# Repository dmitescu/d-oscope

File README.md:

# d-oscope
Digital oscilloscope project, which can be done with medium knowledge in MCUs and programming.

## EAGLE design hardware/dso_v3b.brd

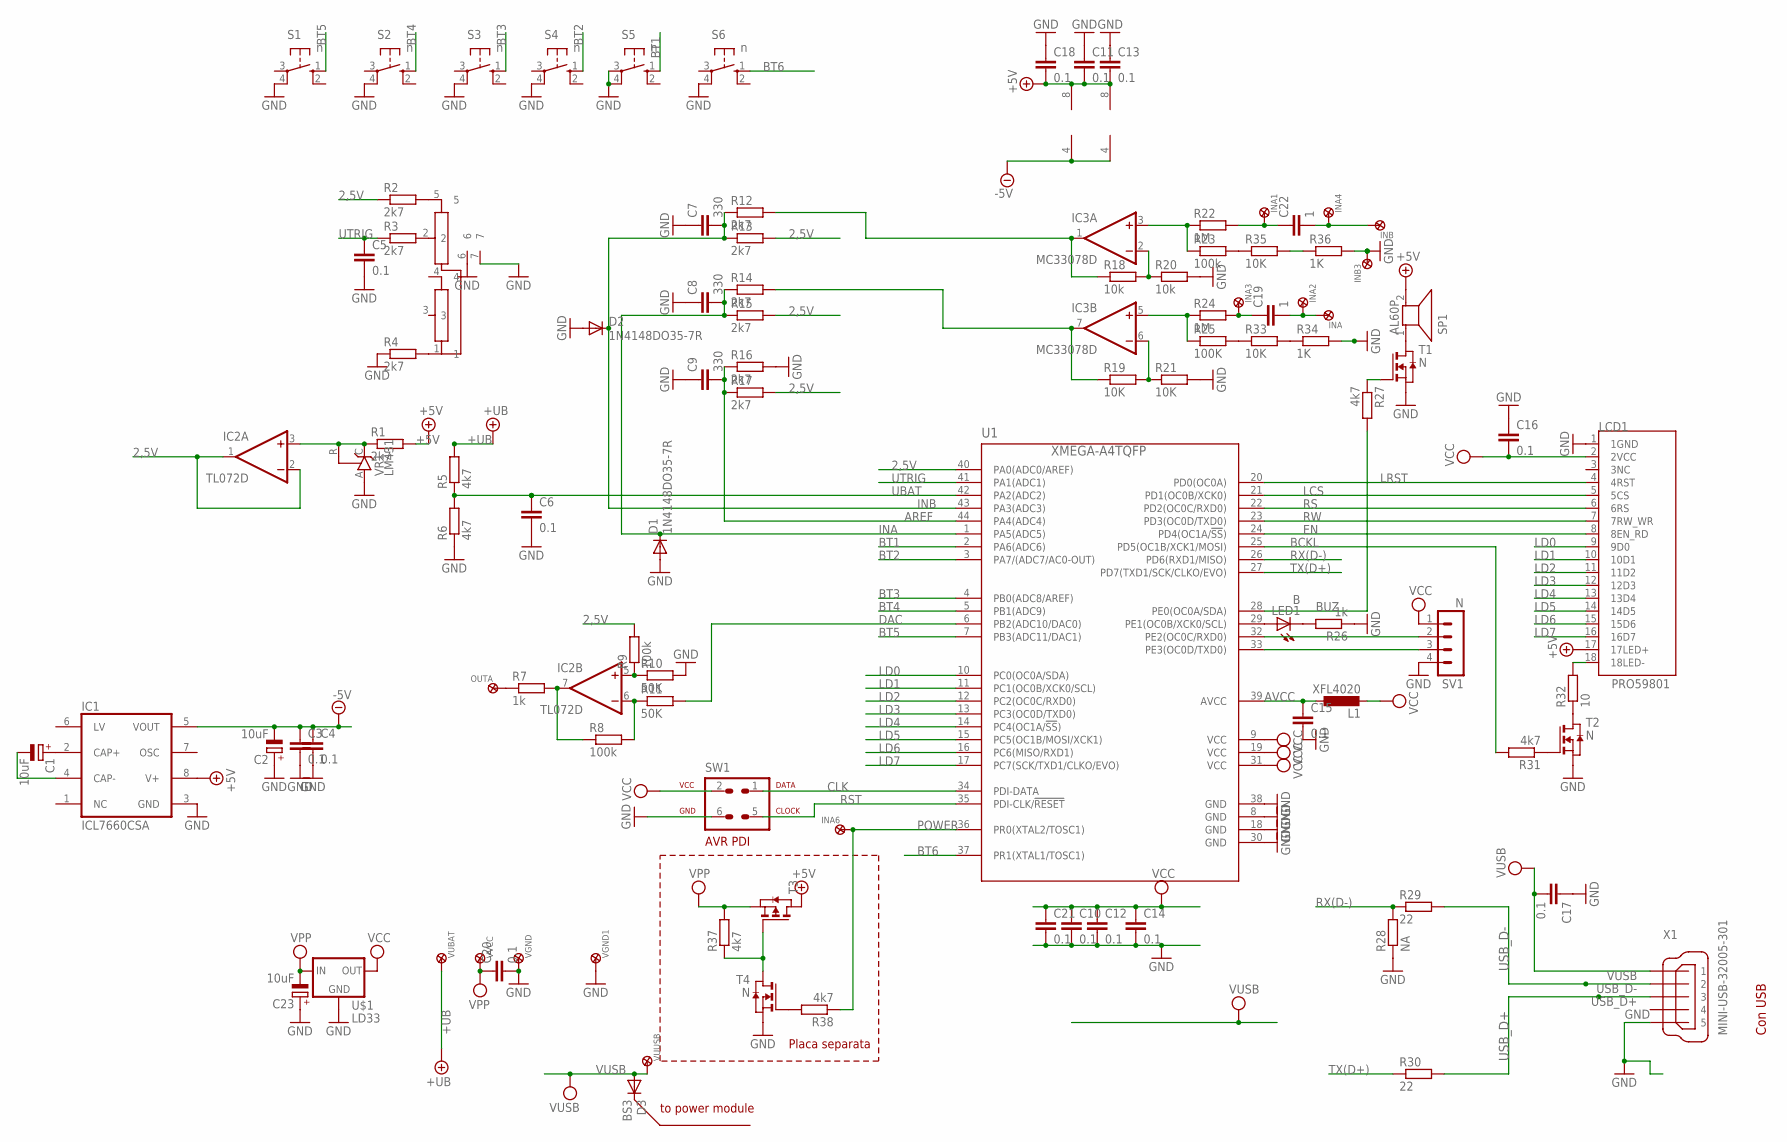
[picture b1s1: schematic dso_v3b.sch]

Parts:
C1, C2, C23: 10uF; CT3528
C3, C4, C5, C6, C10, C11, C12, C14, C15, C16, C18: 0.1; C0603
C7, C8, C9: 330; C025-024X044
C13: 0.1; SMD_SPECIAL
C17: 0.1; C1206
C19, C22: 1; C0603
C20, C21: 0.1; C0805
D1, D2: 1N4148DO35-7R; DO35-7R
D3: BS3; DO35-7R
IC1: ICL7660CSA; SO08
IC2: TL072D; SO08
IC3: MC33078D; SO08
INA, INA6: PADR1; LP1
INA1, INA2, INA3, INA4: PADR; LP
INB, INB3: PADR1; LP1
L1: XFL4020
LCD1: PRO59801; PRO59801L
LED1: B; LED3MM
OUTA: PADR1; LP1
P1: POT5P
R1: 2k7; 0204/7
R2, R3, R13, R15: 2k7; R0603
R4, R12, R14, R16, R17: 2k7; SMD_SPECIAL
R5, R6, R31, R37, R38: 4k7; R0603
R7, R26: 1k; R0603
R8, R9, R23: 100k; R0805
R10: 50K; R0805
R11: 50K; SMD_SPECIAL
R18, R20: 10k; R0805
R19, R21, R33, R35: 10K; R0805
R22, R24: 1M; R0805
R25: 100K; R0603
R27: 4k7; 0204/7
R28: NA; R0603
R29, R30: 22; R0603
R32: 10; SMD_SPECIAL
R34, R36: 1K; R0603
S1, S2, S3, S4, S5, S6: n; B3F-10XX
SP1: AL60P
SV1: N; MA04-1R
SW1: AVR-PDIS; AVR-ISP-6S
T1, T2, T4: N; SOT-23
T3: PMOSSOT23; SOT-23
U1: XMEGA-A4TQFP; TQFP44
U$1: LD33; SOT223
VGND, VGND1: PADR1; LP1
VR1: LM431; TO92-CLP
VUBAT: PADR1; LP1
VUUSB: PADR1; LP1
VVCC: PADR1; LP1
X1: MINI-USB-32005-301; 32005-301

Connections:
2,5V: IC2.1 (OUT), IC2.2 (-IN), R2.1, R9.2, R13.2, R15.2, R17.4 (2), U1.40 (PA0(ADC0/AREF))
+5V: C11.2, C13.4 (2), C18.2, IC1.8 (V+), IC2.8 (V+), IC3.8 (V+), LCD1.17 (17LED+), R1.2, SP1.2, T3.1 (D)
+UB: R5.2, VUBAT.P$1
-5V: C2.-, C3.1, C4.1, IC1.5 (VOUT), IC2.4 (V-), IC3.4 (V-)
AREF: C9.2, R16.3 (1), R17.3 (1), U1.44 (PA4(ADC4))
AVCC: C15.1, L1.P$1 (1), U1.39 (AVCC)
BCKL: R31.2, U1.25 (PD5(OC1B/XCK1/MOSI))
BT1: S5.1 (S), U1.2 (PA6(ADC6))
BT2: S4.1 (S), U1.3 (PA7/(ADC7/AC0-OUT))
BT3: S3.1 (S), U1.4 (PB0(ADC8/AREF))
BT4: S2.1 (S), U1.5 (PB1(ADC9))
BT5: S1.1 (S), U1.7 (PB3(ADC11/DAC1))
BT6: S6.1 (S), U1.37 (PR1(XTAL1/TOSC1))
BUZ: R27.2, U1.28 (PE0(OC0A/SDA))
CLK: SW1.1, U1.34 (PDI-DATA)
DAC: R11.4 (2), U1.6 (PB2(ADC10/DAC0))
EN: LCD1.8 (8EN_RD), U1.24 (PD4(OC1A/!SS!))
GND: C2.+, C3.2, C4.2, C5.2, C6.2, C7.1, C8.1, C9.1, C10.2, C11.1, C12.2, C13.3 (1), C14.2, C15.2, C16.1, C17.1, C18.1, C20.2, C21.2, C23.+, D1.A, D2.A, IC1.3 (GND), INB3.P$1, LCD1.1 (1GND), P1.6, P1.7, R4.3 (1), R6.1, R10.2, R16.4 (2), R20.2, R21.2, R26.1, R28.1, R34.2, R36.2, S1.4 (P1), S2.4 (P1), S3.4 (P1), S4.4 (P1), S5.3, S5.4 (P1), S6.4 (P1), SV1.4, SW1.6, T1.2 (S), T2.2 (S), T4.2 (S), U1.8 (GND), U1.18 (GND), U1.30 (GND), U1.38 (GND), U$1.1 (GND), VGND.P$1, VGND1.P$1, VR1.A, X1.5
INA: C8.2, D1.C, R14.3 (1), R15.1, U1.1 (PA5(ADC5))
INB: C7.2, D2.C, R12.3 (1), R13.1, U1.43 (PA3(ADC3))
LCS: LCD1.5 (5CS), U1.21 (PD1(OC0B/XCK0))
LD0: LCD1.9 (9D0), U1.10 (PC0(OC0A/SDA))
LD1: LCD1.10 (10D1), U1.11 (PC1(OC0B/XCK0/SCL))
LD2: LCD1.11 (11D2), U1.12 (PC2(OC0C/RXD0))
LD3: LCD1.12 (12D3), U1.13 (PC3(OC0D/TXD0))
LD4: LCD1.13 (13D4), U1.14 (PC4(OC1A/!SS!))
LD5: LCD1.14 (14D5), U1.15 (PC5(OC1B/MOSI/XCK1))
LD6: LCD1.15 (15D6), U1.16 (PC6(MISO/RXD1))
LD7: LCD1.16 (16D7), U1.17 (PC7(SCK/TXD1/CLKO/EVO))
LRST: LCD1.4 (4RST), U1.20 (PD0(OC0A))
unnamed: C1.+, IC1.2 (CAP+)
unnamed: C1.-, IC1.4 (CAP-)
unnamed: R37.1, T3.3 (G), T4.1 (D)
unnamed: IC2.3 (+IN), R1.1, VR1.C, VR1.R
unnamed: R38.2, T4.3 (G)
unnamed: LED1.A, U1.29 (PE1(OC0B/XCK0/SCL))
unnamed: SV1.2, U1.32 (PE2(OC0C/RXD0))
unnamed: SV1.3, U1.33 (PE3(OC0D/TXD0))
unnamed: R27.1, T1.3 (G)
unnamed: LCD1.18 (18LED-), R32.4 (2)
unnamed: R32.3 (1), T2.1 (D)
unnamed: R31.1, T2.3 (G)
unnamed: R33.2, R34.1
unnamed: P1.1, R4.4 (2)
unnamed: P1.5, R2.2
unnamed: IC3.1 (OUT), R12.4 (2), R18.1
unnamed: IC3.7 (OUT), R14.4 (2), R19.1
unnamed: P1.2, R3.2
unnamed: IC3.3 (+IN), R22.1, R23.1
unnamed: IC3.2 (-IN), R18.2, R20.1
unnamed: IC3.5 (+IN), R24.1, R25.1
unnamed: IC3.6 (-IN), R19.2, R21.1
unnamed: C22.2, INA4.P$1, INB.P$1
unnamed: C19.2, INA.P$1, INA2.P$1
unnamed: IC2.5 (+IN), R9.1, R10.1
unnamed: IC2.6 (-IN), R8.2, R11.3 (1)
unnamed: IC2.7 (OUT), R7.2, R8.1
unnamed: OUTA.P$1, R7.1
unnamed: SP1.1, T1.1 (D)
unnamed: LED1.K (C), R26.2
unnamed: C19.1, INA3.P$1, R24.2
unnamed: R25.2, R33.1
unnamed: R23.2, R35.1
unnamed: R35.2, R36.1
unnamed: C22.1, INA1.P$1, R22.2
POWER: INA6.P$1, R38.1, U1.36 (PR0(XTAL2/TOSC1))
RS: LCD1.6 (6RS), U1.22 (PD2(OC0C/RXD0))
RST: SW1.5, U1.35 (PDI-CLK/!RESET)
RW: LCD1.7 (7RW_WR), U1.23 (PD3(OC0D/TXD0))
RX(D-): R28.2, R29.1, U1.26 (PD6(RXD1/MISO))
TX(D+): R30.1, U1.27 (PD7(TXD1/SCK/CLKO/EVO))
UBAT: C6.1, R5.1, R6.2, U1.42 (PA2(ADC2))
USB_D+: R30.2, X1.3
USB_D-: R29.2, X1.2
UTRIG: C5.1, R3.1, U1.41 (PA1(ADC1))
VCC: C10.1, C12.1, C14.1, C16.2, C21.1, L1.P$2 (2), LCD1.2 (2VCC), SV1.1, SW1.2, U1.9 (VCC), U1.19 (VCC), U1.31 (VCC), U$1.2 (OUT), U$1.4 (OUT)
VPP: C20.1, C23.-, R37.2, T3.2 (S), U$1.3 (IN), VVCC.P$1
VUSB: C17.2, D3.A, VUUSB.P$1, X1.1

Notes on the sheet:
Con USB
to power module
Placa separata

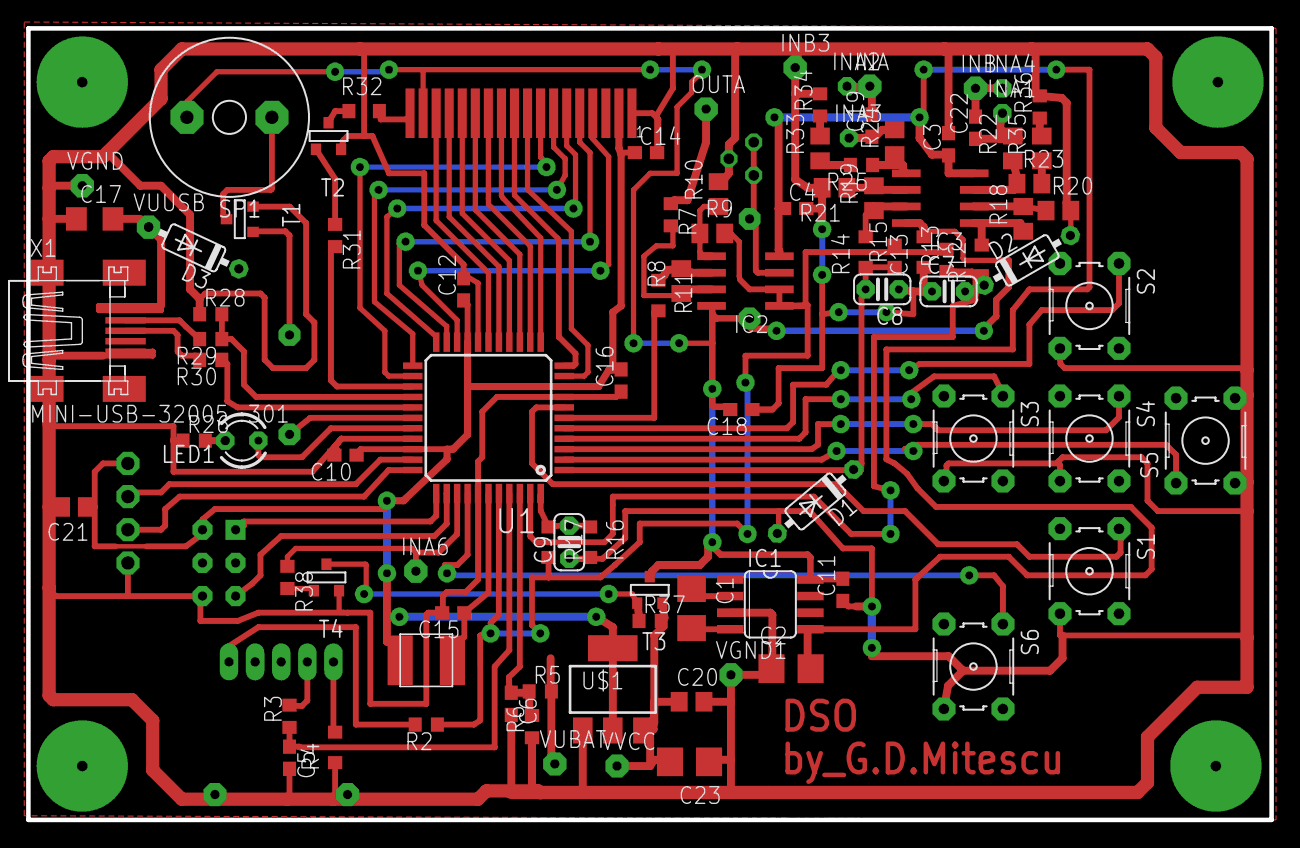
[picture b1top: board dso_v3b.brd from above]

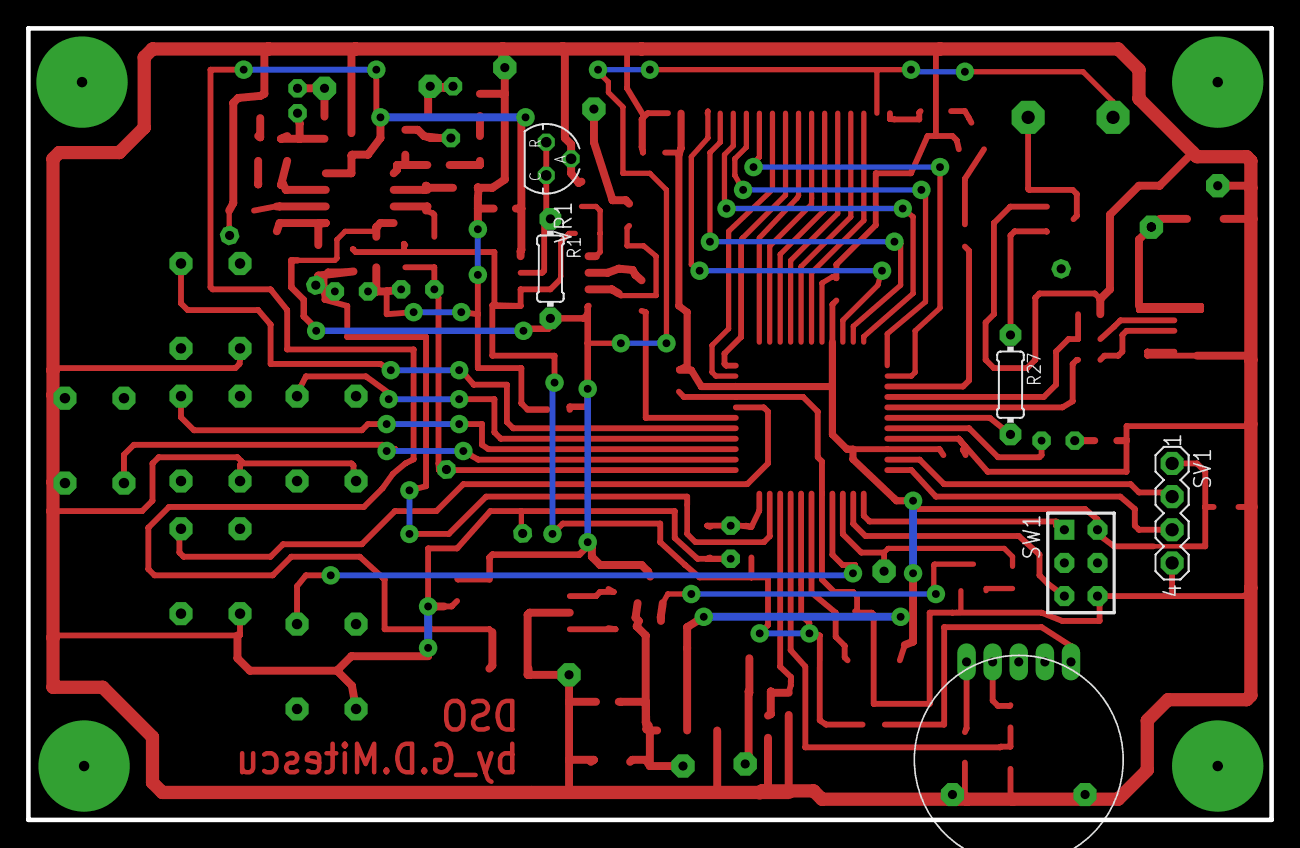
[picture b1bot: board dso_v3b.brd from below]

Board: 3 copper layers, 95.2 x 60.6 mm, 102 parts (6 on the bottom side), 78 nets.

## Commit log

2015-08-18 Reorganized files from previous project...
2015-08-18 Updated inclusion of headers...
2015-08-18 Added naibe make files...
2015-08-19 Fixed autotools stuff
2015-08-19 Slight modifications...
